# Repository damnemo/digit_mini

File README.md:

DIGIT MINI
====================

Schema elettrico e pcb di un mini digit a led 
controllato con shift register 74HC595

Per la visualizzazione dei file `sch e brd` 
usare eagle, programma per il design di pcb.

Per la visualizzazione del file 3D `eagleUp/mini_digit.skp`
usare il programma google sketchup.

	git clone git@github.com:damnemo/digit_mini.git
	git clone git://github.com/damnemo/digit_mini.git

## SOFTWARE DA INSTALLARE
 1. `Eagle` , cad for pcb design
 2. `Sketchup` , per modellazione 3D

### EAGLE SCHEMA
NOTA: Diodi in parallelo possono avere delle tensioni 
di soglia un po' diverse e quindi la polarizzazione può 
essere leggermente dissimmetrica... si consiglia di mettere
una resistenza per ogni ramo e non una per entrambi i rami.

### BOARD BOTTOM

### 3D IMAGE CON GOOGLE SKETCHUP

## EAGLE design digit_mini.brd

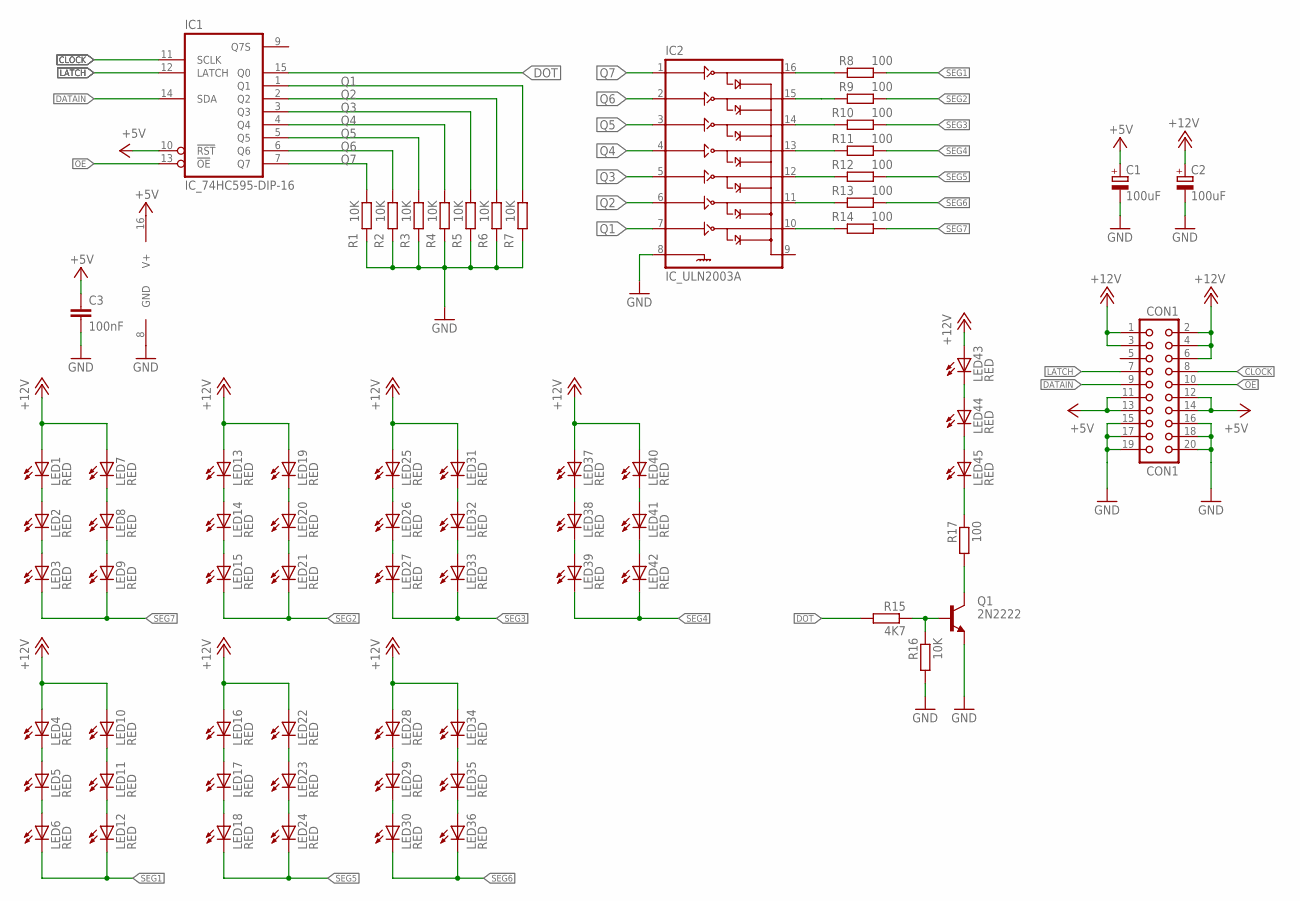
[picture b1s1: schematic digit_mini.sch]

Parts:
C1, C2: 100uF; E2,5-7
C3: 100nF; C050-025X075
CON1: CON1; CON20
IC1: IC_74HC595-DIP-16; DIL16
IC2: IC_ULN2003A; DIL16
LED1, LED2, LED3, LED4, LED5, LED6, LED7, LED8, LED9, LED10, LED11, LED12, LED13, LED14, LED15, LED16, LED17, LED18, LED19, LED20, LED21, LED22, LED23, LED24, LED25, LED26, LED27, LED28, LED29, LED30, LED31, LED32, LED33, LED34, LED35, LED36, LED37, LED38, LED39, LED40, LED41, LED42, LED43, LED44, LED45: RED; LED5MM
Q1: 2N2222; TO92-E1
R1, R2, R3, R4, R5, R6, R7, R16: 10K; 0207/12
R8, R9, R10, R11, R12, R13, R14, R17: 100; 0207/12
R15: 4K7; 0207/12

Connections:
+5V: C1.+, C3.1, CON1.11, CON1.12, CON1.13, CON1.14, IC1.10 (!RST), IC1.16 (V+)
+12V: C2.+, CON1.1, CON1.2, CON1.3, CON1.4, CON1.6, LED1.A, LED4.A, LED7.A, LED10.A, LED13.A, LED16.A, LED19.A, LED22.A, LED25.A, LED28.A, LED31.A, LED34.A, LED37.A, LED40.A, LED43.A
CLOCK: CON1.8, IC1.11 (SCLK)
DATAIN: CON1.9, IC1.14 (SDA)
DOT: IC1.15 (Q0), R15.2
GND: C1.-, C2.-, C3.2, CON1.15, CON1.16, CON1.17, CON1.18, CON1.19, CON1.20, IC1.8 (GND), IC2.8 (GND), Q1.3 (E), R1.2, R2.2, R3.2, R4.1, R5.1, R6.1, R7.1, R16.2
LATCH: CON1.7, IC1.12 (LATCH)
unnamed: LED45.K (C), R17.1
unnamed: Q1.1 (C), R17.2
unnamed: IC2.15 (2C), R9.2
unnamed: LED13.K (C), LED14.A
unnamed: LED14.K (C), LED15.A
unnamed: IC2.14 (3C), R10.2
unnamed: IC2.13 (4C), R11.2
unnamed: LED19.K (C), LED20.A
unnamed: LED20.K (C), LED21.A
unnamed: IC2.12 (5C), R12.2
unnamed: IC2.11 (6C), R13.2
unnamed: IC2.10 (7C), R14.2
unnamed: LED25.K (C), LED26.A
unnamed: IC2.16 (1C), R8.2
unnamed: LED26.K (C), LED27.A
unnamed: LED1.K (C), LED2.A
unnamed: LED2.K (C), LED3.A
unnamed: LED7.K (C), LED8.A
unnamed: LED8.K (C), LED9.A
unnamed: LED31.K (C), LED32.A
unnamed: LED32.K (C), LED33.A
unnamed: LED37.K (C), LED38.A
unnamed: LED38.K (C), LED39.A
unnamed: LED40.K (C), LED41.A
unnamed: LED41.K (C), LED42.A
unnamed: LED16.K (C), LED17.A
unnamed: LED17.K (C), LED18.A
unnamed: LED22.K (C), LED23.A
unnamed: LED23.K (C), LED24.A
unnamed: LED28.K (C), LED29.A
unnamed: LED29.K (C), LED30.A
unnamed: LED34.K (C), LED35.A
unnamed: LED35.K (C), LED36.A
unnamed: LED4.K (C), LED5.A
unnamed: LED5.K (C), LED6.A
unnamed: LED10.K (C), LED11.A
unnamed: LED11.K (C), LED12.A
unnamed: LED43.K (C), LED44.A
unnamed: Q1.2 (B), R15.1, R16.1
unnamed: LED44.K (C), LED45.A
OE: CON1.10, IC1.13 (!OE)
Q1: IC1.1 (Q1), IC2.7 (7B), R7.2
Q2: IC1.2 (Q2), IC2.6 (6B), R6.2
Q3: IC1.3 (Q3), IC2.5 (5B), R5.2
Q4: IC1.4 (Q4), IC2.4 (4B), R4.2
Q5: IC1.5 (Q5), IC2.3 (3B), R3.1
Q6: IC1.6 (Q6), IC2.2 (2B), R2.1
Q7: IC1.7 (Q7), IC2.1 (1B), R1.1
SEG1: LED6.K (C), LED12.K (C), R8.1
SEG2: LED15.K (C), LED21.K (C), R9.1
SEG3: LED27.K (C), LED33.K (C), R10.1
SEG4: LED39.K (C), LED42.K (C), R11.1
SEG5: LED18.K (C), LED24.K (C), R12.1
SEG6: LED30.K (C), LED36.K (C), R13.1
SEG7: LED3.K (C), LED9.K (C), R14.1

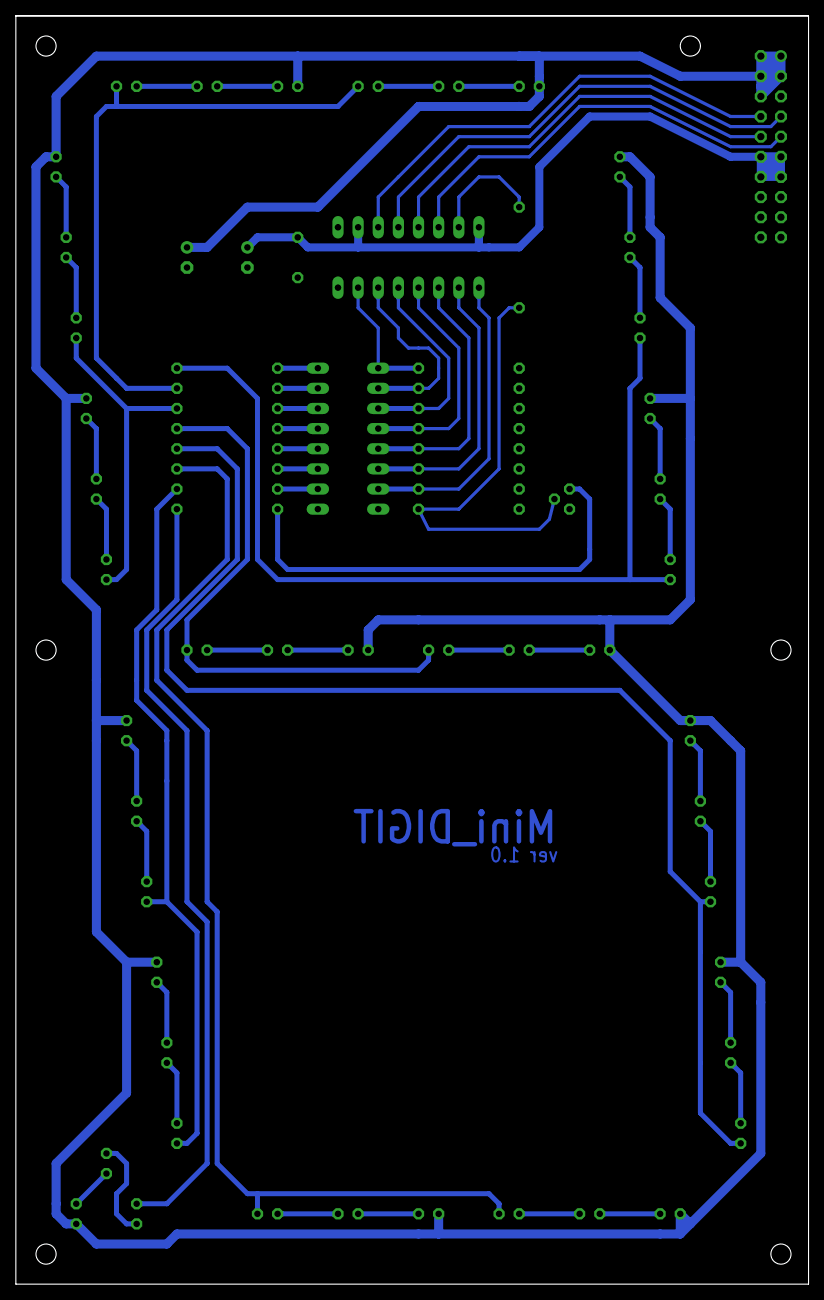
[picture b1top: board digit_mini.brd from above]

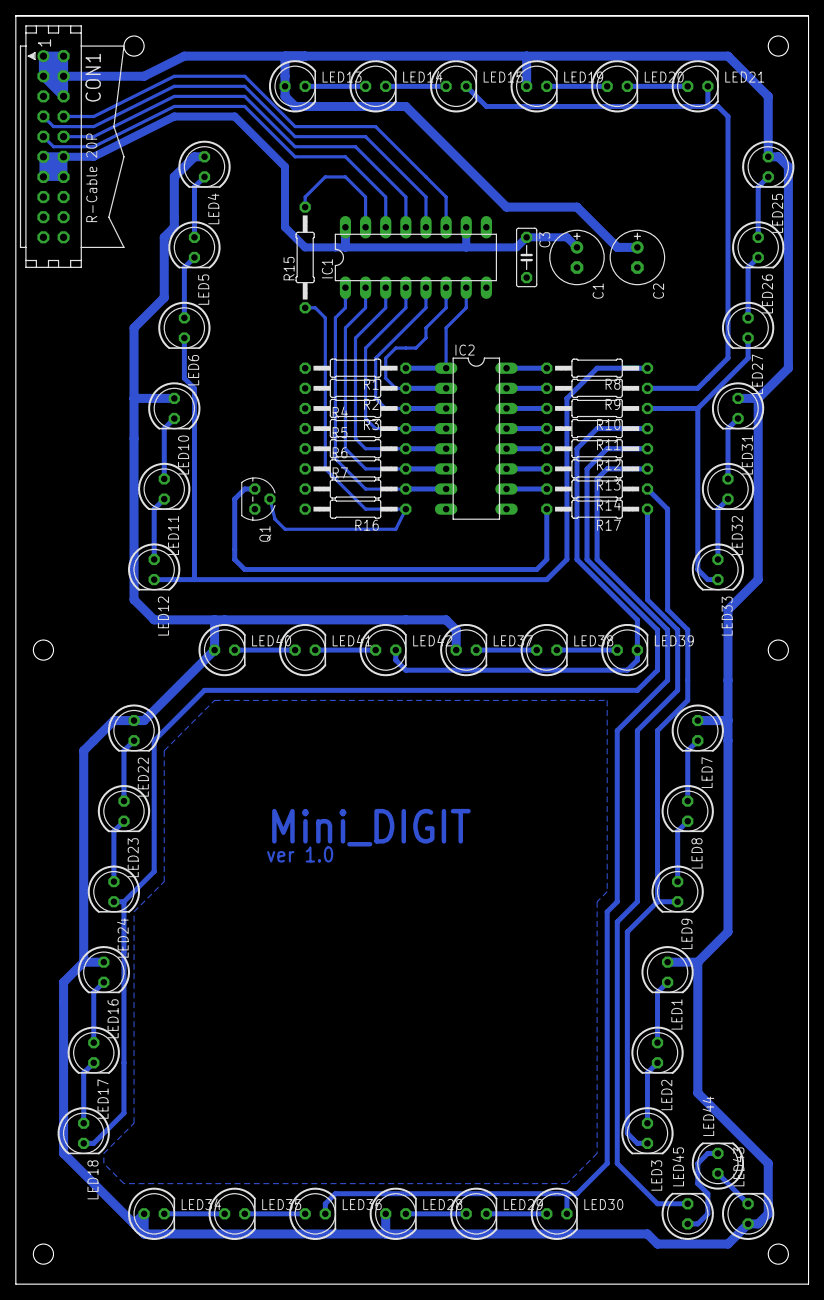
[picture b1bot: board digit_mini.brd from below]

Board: 2 copper layers, 100.0 x 160.0 mm, 70 parts (69 on the bottom side), 62 nets.

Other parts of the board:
U$1: LOGO_DAM+

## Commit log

2017-09-23 Create LICENSE
